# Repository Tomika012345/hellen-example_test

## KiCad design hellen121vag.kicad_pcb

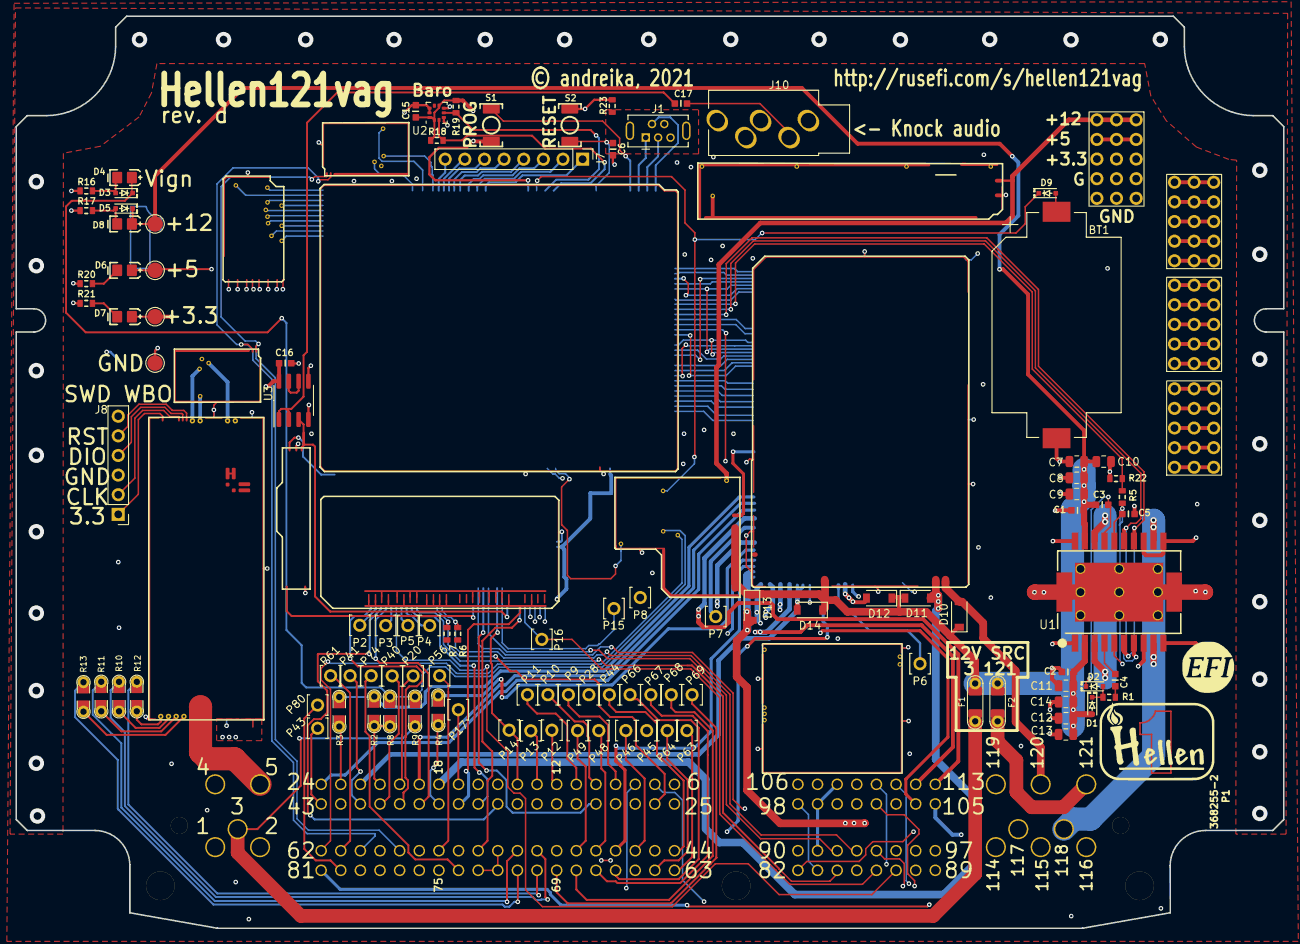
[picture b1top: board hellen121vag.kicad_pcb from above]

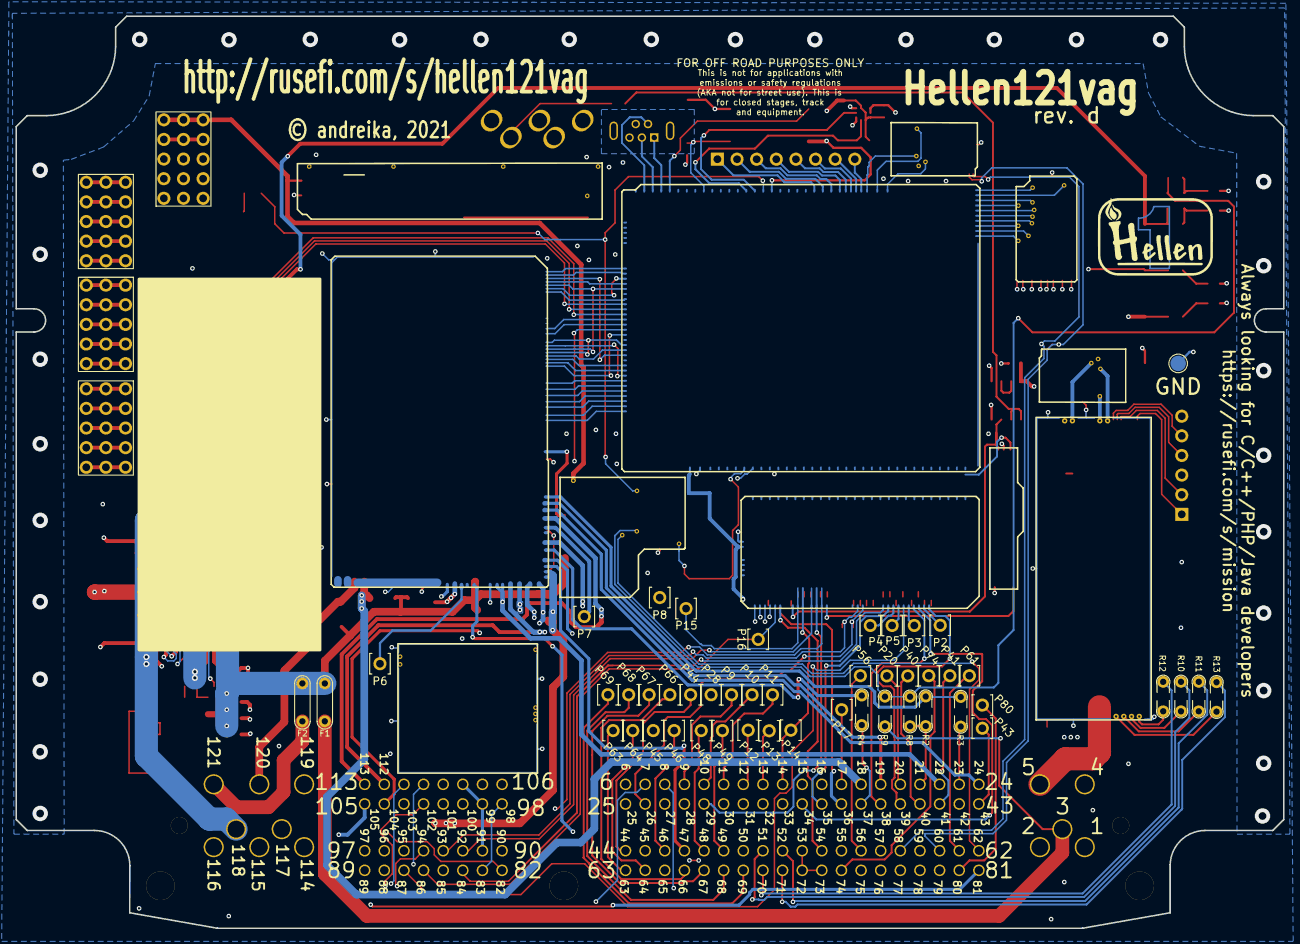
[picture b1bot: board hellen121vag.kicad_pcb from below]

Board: 4 copper layers, 164.0 x 118.0 mm, 124 parts (2 on the bottom side), 230 nets.

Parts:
BT1: BATTERY_CR2032; BatteryHolder_Keystone_1060_1x2032
C1, C2, C6, C15, C16: 100n; C0603
C3: 220n; C0603
C4: 10n; C0603
C5: 5.6n; C0603
C7, C8, C9, C10, C11, C12, C13, C14: 10u; C_0805_2012Metric
C17: 10u; C0603
D1, D2, D3, D5, D9: 1N4148WS; SOD-323
D4, D6, D7, D8: LED-GREEN-0805; LED-0805
D10, D11, D12, D13, D14: B5819W; D_SOD-123
F1, F2: Fuse-Pad-Pad; PAD-1206-PAD
G1, G2, G3, G5: PROTO_AREA
G4: DISCLAIMER; Off_Road_Disclaimer
G6, G7: LOGO
J1: USB_B_Mini; USB-MINI-B-VERTICAL
J2, J3, J4, J5, J6: Conn_01x01; TestPoint_Pad_D2.0mm
J7: Conn_01x08; PinHeader_1x08_P2.54mm_Vertical
J8: Conn_01x06; PinHeader_1x06_P2.54mm_Vertical
J10: AudioJack_THR; Jack_3.5mm_PJ-3250-5A
M1, M10: Module-can-0.1; can
M2: Module-power5-0.2; power5
M3: Module-mcu-0.7; mcu
M4: Module-input-0.1; input
M5: Module-knock-0.1; knock
M6: Module-output-0.3; output
M7: Module-ign8-0.2; ign8
M8: Module-power12-0.2; power12
M9: Module-wbo-0.3; wbo
M11: Module-vr-discrete-0.1; vr-discrete
P1: 368255-2
P2, P3, P4, P5, P6, P7, P8, P9, P10, P11, P12, P13, P14, P15, P16, P17, P20, P28, P40, P41, P43, P44, P45, P46, P48, P49, P56, P61, P63, P64, P66, P67, P68, P69, P74, P80: Pad; PAD-TH
R1: 100; R0603
R2, R3, R4, R8, R9, R10, R11, R12, R13: Jumper-Pad-Pad; PAD-0805-PAD
R5: 100k; R0603
R6, R7: 2.7k; R0603
R16, R17: 5.1k; R0603
R18, R19: 4.7k; R0603
R20: 1.6k; R0603
R21: 750; R0603
R22: 10k; R0603
R23: 0; R0603
S1, S2: Button_SPST; SMD-2_2.9x3.9x1.7
U1: L6205PD; SO20POWER
U2: LPS25HB; ST_HLGA-10_2.5x2.5mm_P0.6mm_LayoutBorder3x2y
U3: MCP6002-xSN; SOIC-8_3.9x4.9mm_P1.27mm

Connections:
+3V3: C15.2, D7.1 (A), G3.3, G3.8, G3.13, J4.1, M3.N16 (V33), R18.1, R19.1, S1.2, U2.1 (VDDio), U2.6 (~CS), U2.10 (VDD)
+5V: C16.2, D6.1 (A), G3.2, G3.7, G3.12, J3.1, M1.V1 (V5), M2.V2 (V5), M3.S1 (V5), M4.E2 (V5), M6.W14 (V5), M8.E1 (V5), M9.W1 (V5_IN), M10.V1 (V5), M11.E4 (V5_IN), U3.8 (V+)
+5VA: M3.S33 (V5A), M4.E5 (V5A), M4.J1 (PULL_V5A), M4.J5 (PULL_PPS), M4.J7 (PULL_AUX4), M4.J9 (PULL_AUX2), M4.J10 (PULL_AUX1), M4.J17 (PULL_CAM), M4.J18 (PULL_VSS), M4.J19 (PULL_TPS), M4.J20 (PULL_O2S), M4.J21 (PULL_CRANK), M4.N1 (V5A), M5.E1 (V5A), R6.2, R7.2
+5VP: P1.53, P1.72, P1.73, P1.83, P1.98
+12V: G3.1, G3.6, G3.11, M2.V1 (V12), M8.V1 (V12)
+12V_RAW: C1.2, C2.2, C3.2, C7.2, C8.2, C9.2, C10.2, C11.2, C12.2, C13.2, C14.2, D1.2 (A), D5.1 (K), D8.1 (A), D10.1 (K), D11.1 (K), D12.1 (K), D13.1 (K), D14.1 (K), F1.2, F2.2, J2.1, M6.S11 (V12_RAW), M8.E2 (V12_RAW), U1.2 (VSA), U1.19 (VSB)
/+ETB: M3.E14 (OUT_PWM2), U1.7 (IN2A), U1.15 (IN2B)
/+ETB_OUT: P1.117, U1.3 (OUT2A), U1.18 (OUT2B)
/-ETB: M3.E15 (OUT_PWM3), U1.6 (IN1A), U1.14 (IN1B)
/-ETB_OUT: P1.118, U1.9 (OUT1A), U1.12 (OUT1B)
/A1: M3.S30 (IN_O2S2), M4.N4 (O2S2)
/A2: M3.S22 (IN_MAP3), M4.N12 (MAP3)
/A3: M3.S26 (IN_AUX3), M4.N8 (AUX3)
/A4: M3.S23 (IN_DIG3), M4.N11 (RES3)
/AFR: M3.S16 (IN_O2S), M4.N18 (O2S)
/BOOT0: M3.N28 (BOOT0), S1.1
/CAM1: M3.S15 (IN_AN_DIG2), M4.N19 (CAM)
/CAM2: M3.S27 (IN_AUX4), M4.N7 (AUX4)
/CAN+: M1.S2 (CANH), M10.S2 (CANH), P1.60
/CAN-: M1.S1 (CANL), M10.S1 (CANL), P1.58
/CAN_RX: M1.V6 (CAN_RX), M3.N2 (CAN_RX)
/CAN_TX: M1.V5 (CAN_TX), M3.N3 (CAN_TX)
/CAN_VIO: M1.V2 (CAN_VIO), M3.N1 (CAN_VIO)
/CHECK_ENGINE: M3.E22 (OUT_IO8), M6.W25 (LOW6_DIODE)
/CLT: M3.S18 (IN_CLT), M4.N16 (CLT)
/CRANK: M3.S13 (IN_AN_DIG1), M4.N21 (CRANK)
/D1: M3.S3 (IN_DIG8), M4.N26 (SENS1)
/D2: M3.S4 (IN_DIG9), M4.N25 (SENS2)
/D3: M3.S5 (IN_DIG10), M4.N24 (SENS3)
/D4: M3.S6 (IN_DIG11), M4.N23 (SENS4)
/ETB_EN: M3.E13 (OUT_IO12), R5.1, R22.1
/FUEL_CONSUM: M3.E19 (OUT_PWM7), M6.W22 (PP2)
/FUEL_PUMP_RELAY: M3.E8 (OUT_IO1), M6.W35 (LOW11)
/IAT: M3.S19 (IN_IAT), M4.N15 (IAT)
/IDLE: M3.E23 (OUT_IO4), M6.W38 (LOW3_DUAL)
/IGN1: M3.W1 (OUT_IGN1), M7.V8 (IGN1)
/IGN2: M3.W2 (OUT_IGN2), M7.V7 (IGN2)
/IGN3: M3.W3 (OUT_IGN3), M7.V6 (IGN3)
/IGN4: M3.W4 (OUT_IGN4), M7.V5 (IGN4)
/IGN5: M3.W5 (OUT_IGN5), M7.V4 (IGN5)
/IGN6: M3.W6 (OUT_IGN6), M7.V3 (IGN6)
/IGN7: M3.W7 (OUT_IGN7), M7.V2 (IGN7)
/IGN8: M3.W8 (OUT_IGN8), M7.V1 (IGN8)
/IGN_V5: M3.W9 (IGN_V5), M7.V9 (VCC)
/IGN_V33: M3.W10 (IGN_V33), M7.V10 (V33)
/INJ1: M3.E25 (OUT_INJ1), M6.W24 (INJ1)
/INJ2: M3.E26 (OUT_INJ2), M6.W23 (INJ2)
/INJ3: M3.E29 (OUT_INJ3), M6.W20 (INJ3)
/INJ4: M3.E30 (OUT_INJ4), M6.W19 (INJ4)
/INJ5: M3.E31 (OUT_INJ5), M6.W18 (INJ5)
/INJ6: M3.E32 (OUT_INJ6), M6.W17 (INJ6)
/INJ7: M3.E33 (OUT_INJ7), M6.W16 (INJ7)
/INJ8: M3.E34 (OUT_INJ8), M6.W15 (INJ8)
/IN_A1: M4.S25 (IN_O2S2), P2.1
/IN_A2: M4.S19 (IN_MAP3), P4.1
/IN_A3: M4.S20 (IN_AUX3), P5.1
/IN_A4: M4.S22 (IN_RES3), P3.1
/IN_AFR: M4.S9 (IN_O2S), P1.14, P14.1
/IN_CAM1: M4.S5 (IN_CAM), P1.86, P16.1
/IN_CAM2: M4.S21 (IN_AUX4), P1.87
/IN_CLT: M4.S15 (IN_CLT), P1.93, R6.1
/IN_CRANK: M4.S8 (IN_CRANK), M11.E3 (OUT), P15.1
/IN_CRANK+: M11.W2 (VR+), P1.82
/IN_CRANK-: M11.W1 (VR-), P1.90
/IN_D1: M4.S1 (IN_SENS1), P1.55
/IN_D2: M4.S2 (IN_SENS2), P1.57
/IN_D3: M4.S3 (IN_SENS3), P1.75
/IN_D4: M4.S4 (IN_SENS4), P1.76
/IN_IAT: M4.S16 (IN_IAT), P1.26, P1.85, R7.1
/IN_KNOCK1: M4.S7 (IN_KNOCK), M5.E3 (OUT_KNOCK), U3.3 (+)
/IN_KNOCK1_RAW: M5.W1 (IN_KNOCK), P1.106
/IN_MAF: M4.S11 (IN_MAP1), P1.29
/IN_MAP2: M4.S12 (IN_MAP2), P1.101
/IN_PPS1: M4.S24 (IN_PPS), P1.34
/IN_PPS2: M4.S18 (IN_AUX2), P1.35
/IN_RES1: M4.S23 (IN_RES1), P1.38
/IN_RES2: M4.S26 (IN_RES2), P1.39
/IN_TPS1: M4.S10 (IN_TPS), P1.92
/IN_TPS2: M4.S17 (IN_AUX1), P1.84
/IN_VIGN: D3.1 (K), D4.1 (A), M8.V3 (IN_VIGN), R8.1, R9.2
/IN_VSS: M4.S6 (IN_VSS), P1.54
/KNOCK1: M3.S12 (IN_KNOCK), M4.N22 (KNOCK)
/LSU_CALIBR_RES: M9.E4 (LSU_Rtrim), R13.2
/LSU_HEAT-: M9.E5 (LSU_H+), P1.5
/LSU_PUMP_I: M9.E3 (LSU_Ip), R11.2
/LSU_SENSOR_U: M9.E1 (LSU_Un), R12.2
/LSU_SENSOR_U/PUMP_I: M9.E2 (LSU_Vm), R10.2
/MAF: M3.S20 (IN_MAP1), M4.N14 (MAP1)
/MAIN_RELAY: M3.E6 (OUT_IO3), M6.W40 (LOW5_MAIN)
/MAP2: M3.S21 (IN_MAP2), M4.N13 (MAP2)
/NRESET: C6.2, M3.N24 (nReset), S2.1
/OUT1: M3.E7 (OUT_IO5), M6.W39 (LOW7_HIGH1)
/OUT2: M3.E9 (OUT_IO6), M6.W37 (LOW8_HIGH2)
/OUT3: M3.E28 (OUT_PWM8), M6.W21 (LOW1)
/OUT_CHECK_ENGINE: M6.W3 (OUT_LOW6_DIODE), P1.47
/OUT_FUEL_CONSUM: M6.S6 (OUT_PP2), P1.81
/OUT_FUEL_PUMP_RELAY: M6.S10 (OUT_LOW11), P1.65
/OUT_IDLE: D12.2 (A), M6.S7 (OUT_LOW3_DUAL), P1.105
/OUT_IGN1: M7.S8 (OUT_IGN1), P1.102
/OUT_IGN2: M7.S7 (OUT_IGN2), P1.7
/OUT_IGN3: M7.S6 (OUT_IGN3), P1.111
/OUT_IGN4: M7.S5 (OUT_IGN4), P1.94
/OUT_IGN5: M7.S4 (OUT_IGN5), P1.103
/OUT_IGN6: M7.S3 (OUT_IGN6), P1.110
/OUT_IGN7: M7.S2 (OUT_IGN7), P1.8
/OUT_IGN8: M7.S1 (OUT_IGN8), P1.95
/OUT_INJ1: M6.S18 (OUT_INJ1), P1.96
/OUT_INJ2: M6.S16 (OUT_INJ2), P1.89
/OUT_INJ3: M6.S17 (OUT_INJ3), P1.97
/OUT_INJ4: M6.W7 (OUT_INJ4), P1.88
/OUT_INJ5: M6.W10 (OUT_INJ5), P1.113
/OUT_INJ6: M6.S15 (OUT_INJ6), P1.112
/OUT_INJ7: M6.W12 (OUT_INJ7), P1.19
/OUT_INJ8: M6.W11 (OUT_INJ8), P1.24
/OUT_MAIN_RELAY: M6.W13 (OUT_LOW5_MAIN), R2.2, R3.1
/OUT_TACH: M6.W6 (OUT_PP1), R4.2
/OUT_VVT1_1: D14.2 (A), M6.S13 (OUT_LOW12), M6.S14 (OUT_LOW9), P1.22
/OUT_VVT1_2: D13.2 (A), M6.W1 (OUT_LOW2), M6.W2 (OUT_LOW10), P1.115
/OUT_VVT2_B1: D11.2 (A), M6.S5 (OUT_SOLENOID_B2), P1.18
/OUT_VVT2_B2: D10.2 (A), M6.S4 (OUT_SOLENOID_B1), P1.120
/OUT_WASTEGATE: M6.W4 (OUT_LOW4_DUAL), P1.104
/PPS1: M3.S29 (IN_PPS), M4.N5 (PPS)
/PPS2: M3.S25 (IN_AUX2), M4.N9 (AUX2)
/RES1: M3.S28 (IN_DIG1), M4.N6 (RES1)
/RES2: M3.S31 (IN_DIG2), M4.N3 (RES2)
/RX1: J7.7, M3.N5 (UART8_RX)
/RX2: J7.5, M3.N7 (UART2_RX)
/SPI3_CS: J7.4, M3.N8 (SPI3_CS)
/SPI3_MISO: J7.2, M3.N10 (SPI3_MISO)
/SPI3_MOSI: J7.1, M3.N11 (SPI3_MOSI)
/SPI3_SCK: J7.3, M3.N9 (SPI3_SCK)
/TACH: M3.E27 (OUT_PWM1), M6.W28 (PP1)
/THRESHOLD_VR: M3.E18 (OUT_PWM6), M11.E1 (Thresh_IN)
/TPS1: M3.S17 (IN_TPS), M4.N17 (TPS)
/TPS2: M3.S24 (IN_AUX1), M4.N10 (AUX1)
/TX1: J7.8, M3.N4 (UART8_TX)
/TX2: J7.6, M3.N6 (UART2_TX)
/USBM: J1.2 (D-), M3.N31 (USB1M)
/USBP: J1.3 (D+), M3.N30 (USB1P)
/V12_PERM: M8.V4 (V12_PERM), P1.62
/VBAT: D9.1 (K), M3.N17 (VBAT), M8.V2 (VBAT)
/VBUS: J1.1 (VBUS), M3.N29 (VBUS)
/VIGN: M3.S7 (VIGN), M8.V5 (VIGN)
/VREF2: M4.S13 (VREF2), M5.W2 (VREF)
/VR_ANALOG: M3.S8 (IN_DIG4), M11.E2 (OUT_A)
/VSS: M3.S14 (IN_AN_DIG3), M4.N20 (VSS)
/VVT1_1: M3.E10 (OUT_IO10), M6.W27 (LOW9), M6.W36 (LOW12)
/VVT1_2: M3.E21 (OUT_IO7), M6.W26 (LOW10), M6.W29 (LOW2)
/VVT2_B1: M3.E17 (OUT_PWM5), M6.W30 (SOLENOID_B2)
/VVT2_B2: M3.E16 (OUT_PWM4), M6.W31 (SOLENOID_B1)
/WASTEGATE: M3.E12 (OUT_IO2), M6.W34 (LOW4_DUAL)
GND: BT1.2 (-), C1.1, C2.1, C5.1, C6.1, C7.1, C8.1, C9.1, C10.1, C11.1, C12.1, C13.1, C14.1, C15.1, C16.1, G3.4, G3.5, G3.9, G3.10, G3.14, G3.15, J5.1, J6.1, J8.3, J10.S, M1.E1 (GND), M2.G (GND), M3.S2 (GND), M4.E1 (GND), M5.E2 (GND), M6.G (GND), M6.S3 (GND), M7.G (GND), M8.S1 (GND), M9.E6 (LSU_H-), M9.G (GND), M10.E1 (GND), M11.G (GND), P1.1, P1.2, P1.32, P1.59, R16.2, R17.2, R20.2, R21.2, R22.2, R23.2, S2.2, U1.1 (GND@1), U1.8 (SENSEA), U1.10 (GND@2), U1.11 (GND@3), U1.13 (SENSEB), U1.20 (GND@4), U1.SLUG1 (SLUG@1), U1.SLUG2 (SLUG@2), U1.SLUG3 (SLUG@3), U2.3 (GND), U2.5 (SA0/MISO), U2.8 (GND), U2.9 (GND), U3.4 (V-), U3.5 (+)
GNDA: M3.S32 (GNDA), M4.J2 (PULL_GNDA), M4.J3 (PULL_RES2), M4.J4 (PULL_O2S2), M4.J6 (PULL_RES1), M4.J8 (PULL_AUX3), M4.J11 (PULL_RES3), M4.J12 (PULL_MAP3), M4.J13 (PULL_MAP2), M4.J14 (PULL_MAP1), M4.J22 (PULL_KNOCK), M4.J23 (PULL_SENS4), M4.J24 (PULL_SENS3), M4.J25 (PULL_SENS2), M4.J26 (PULL_SENS1), M4.N2 (GNDA), P1.27, P1.33, P1.36, P1.50, P1.91, P1.99, P1.108
unnamed: BT1.1 (+), D9.2 (A)
unnamed: C3.1, D2.1 (K), U1.17 (VBOOT)
unnamed: C4.1, U1.4 (VCP)
unnamed: C4.2, R1.2
unnamed: C5.2, R5.2, U1.5 (ENA), U1.16 (ENB)
unnamed: C17.1, J10.T
unnamed: C17.2, U3.1, U3.2 (-)
unnamed: D1.1 (K), D2.2 (A), R1.1
unnamed: D3.2 (A), D4.2 (K), R16.1
unnamed: D5.2 (A), D8.2 (K), R17.1
unnamed: D6.2 (K), R20.1
unnamed: D7.2 (K), R21.1
unnamed: F1.1, P1.3, R9.1
unnamed: F2.1, P1.121
unnamed: G1.1, G1.6, G1.11
unnamed: G1.5, G1.10, G1.15
unnamed: G1.2, G1.7, G1.12
unnamed: G1.3, G1.8, G1.13
unnamed: G1.4, G1.9, G1.14
unnamed: G2.1, G2.6, G2.11
unnamed: G2.5, G2.10, G2.15
unnamed: G2.2, G2.7, G2.12
unnamed: G2.3, G2.8, G2.13
unnamed: G2.4, G2.9, G2.14
unnamed: G5.1, G5.6, G5.11
unnamed: G5.5, G5.10, G5.15
unnamed: G5.2, G5.7, G5.12
unnamed: G5.3, G5.8, G5.13
unnamed: G5.4, G5.9, G5.14
unnamed: J1.5 (GND), J1.6 (Shield), R23.1
unnamed: J8.1, M9.W8 (V33_OUT)
unnamed: J8.2, M9.W7 (SWCLK)
unnamed: J8.4, M9.W6 (SWDIO)
unnamed: J8.5, M9.W5 (nReset)
unnamed: M9.J2 (SEL2), M9.J_VCC2 (PULL_UP2)
unnamed: M9.W2 (CAN_VIO), M10.V2 (CAN_VIO)
unnamed: M9.W4 (CAN_TX), M10.V5 (CAN_TX)
unnamed: M9.W3 (CAN_RX), M10.V6 (CAN_RX)
unnamed: P1.9, P9.1
unnamed: P1.10, P10.1
unnamed: P1.11, P11.1
unnamed: P1.12, P12.1
unnamed: P1.13, P13.1
unnamed: P1.17, P17.1
unnamed: P1.20, P20.1
unnamed: P1.21, R2.1, R8.2
unnamed: P1.23, R3.2
unnamed: P1.28, P28.1
unnamed: P1.37, R4.1
unnamed: P1.40, P40.1
unnamed: P1.41, P41.1
unnamed: P1.43, P43.1
unnamed: P1.44, P44.1
unnamed: P1.45, P45.1
unnamed: P1.46, P46.1
unnamed: P1.48, P48.1
unnamed: P1.49, P49.1
unnamed: P1.51, R10.1
unnamed: P1.52, R11.1
unnamed: P1.56, P56.1
unnamed: P1.61, P61.1
unnamed: P1.63, P63.1
unnamed: P1.64, P64.1
unnamed: P1.66, P66.1
unnamed: P1.67, P67.1
unnamed: P1.68, P68.1
unnamed: P1.69, P69.1
unnamed: P1.70, R12.1
unnamed: P1.71, R13.1
unnamed: P1.74, P74.1
unnamed: P1.80, P80.1
unnamed: M6.S8 (OUT_LOW1), P6.1
unnamed: M6.W9 (OUT_LOW7_PULLUP), P7.1
unnamed: M6.S12 (OUT_LOW8_PULLUP), P8.1
unnamed: M3.N19 (I2C_SCL), R18.2, U2.2 (SCL/SCLK)
unnamed: M3.N18 (I2C_SDA), R19.2, U2.4 (SDA/MOSI)
unnamed: U3.6 (-), U3.7

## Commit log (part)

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2026-01-16 [skip actions] Auto-generated board v2.1
2026-01-16 GHA says update hellen-one
2026-01-16 GHA says update kicad6-libraries
2026-01-16 Rename bom_replace_88bmw-a.csv to bom_replace_hellen88bmw-a.csv
2026-01-16 Rename board_id_hellen88bmw-a.csv to board_id_hellen88bmw.csv

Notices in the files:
hellen121vag.kicad_pcb:
© andreika, 2021
